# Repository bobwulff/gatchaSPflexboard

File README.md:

# gachaSP Flexboard

This is designed to be used with the Game Boy Advance SP mod created by [Joseph Tompkins](https://ko-fi.com/josephtomkins) called the [Gacha SP](https://www.youtube.com/watch?v=QM45YnBbGOQ).

This flexible circuit board should make wiring the button board to the main board a lot easier.

In addition to this flexboard you will need to source the following boards/parts:
|Part|Link|
|----|----|
|Faceplate and middle layer|[PCB Way](https://www.pcbway.com/project/shareproject/GachaSP_Final_Revision_a49df9d8.html)|
|PCB Board for rewiring (and wiring diagram)|[PCB Way](https://www.pcbway.com/project/shareproject/Custom_button_board_for_GachaSP_fa33171a.html)|
|Laminated GBA SP IPS Screen|[Retro Modding](https://www.retromodding.com/products/game-boy-advance-sp-ips-3-0inch-laminated-lcd)|
|Button Switches 4.8x4.8x4.5|[Aliexpress](https://www.aliexpress.us/item/3256804096997401.html?spm=a2g0o.order_list.order_list_main.29.59ec1802bsgRpf&gatewayAdapt=glo2usa)|
|Speaker|[eBay](https://www.ebay.com/itm/192292888553?_trkparms=amclksrc%3DITM%26aid%3D777008%26algo%3DPERSONAL.TOPIC%26ao%3D1%26asc%3D20230811123856%26meid%3Dfd54ea30a79047f3a256c025f49bf448%26pid%3D101770%26rk%3D1%26rkt%3D1%26itm%3D192292888553%26pmt%3D1%26noa%3D1%26pg%3D4375194%26algv%3DRecentlyViewedItemsV2&_trksid=p4375194.c101770.m146925&_trkparms=parentrq%3Aafa5a31518e0aab88905efafffffd88a%7Cpageci%3A49d20203-f37f-11ee-bd37-e2ac214ea922%7Ciid%3A1%7Cvlpname%3Avlp_homepage)|
|GBA SP Buttons|[Amazon, Affiliate](https://amzn.to/3TEVo3e)|

</br>
Newest version WITHOUT speaker contacts: </br>

</br></br>
Older version WITH speaker contacts: </br>

</br>

</br>

# To purchase
Download a zip file from the RELEASES section and upload straight to [PCB Way](https://pcbway.com) or [JLCPCB](https://jlcpcb.com). Make sure you select FLEX.
</br>

# Video Tutorial by Macho Nacho

</br>
GOOD LUCK!

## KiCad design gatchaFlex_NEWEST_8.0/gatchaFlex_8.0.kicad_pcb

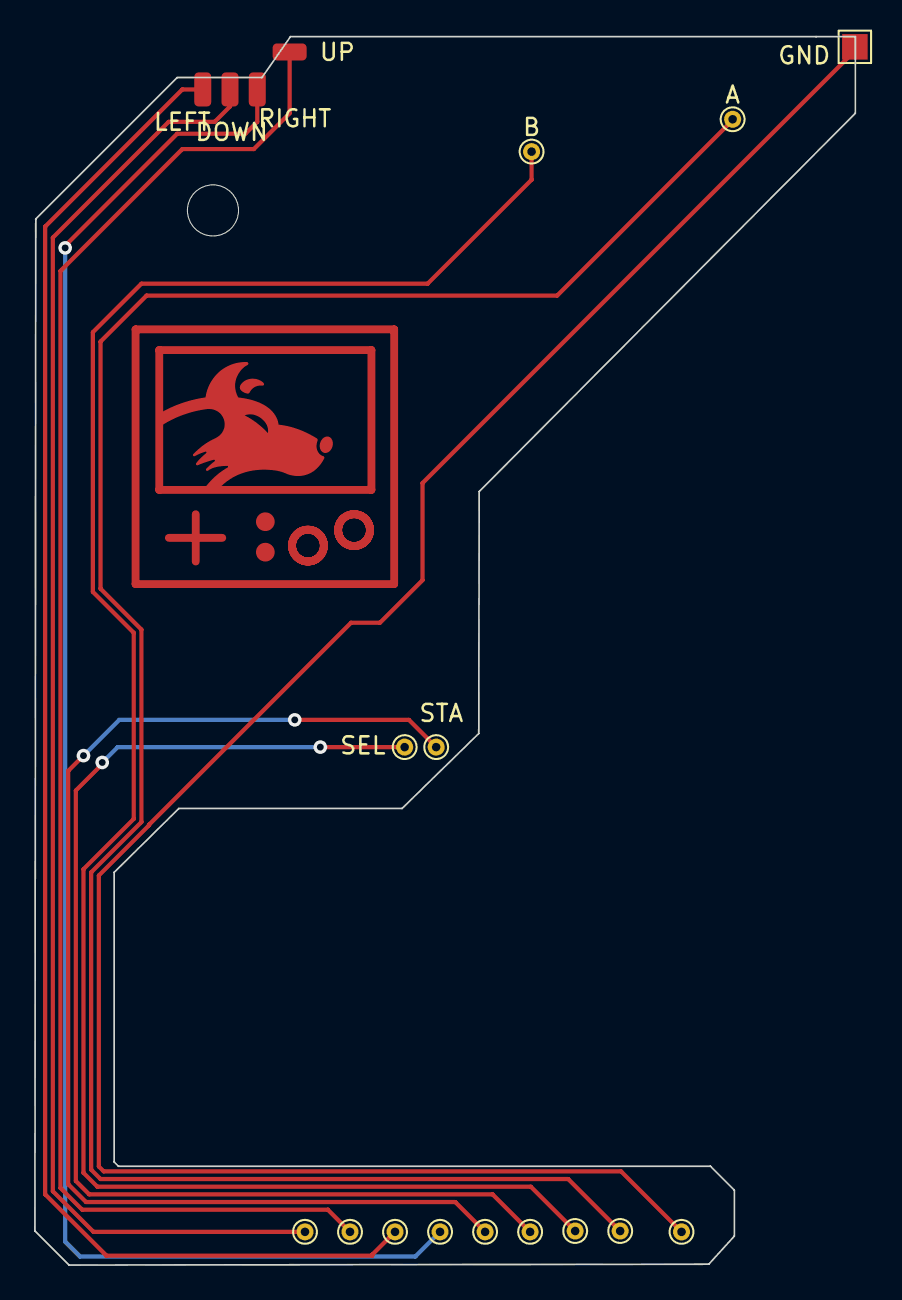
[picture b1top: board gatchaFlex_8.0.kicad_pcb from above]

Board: 2 copper layers, 48.2 x 72.1 mm, 19 parts (0 on the bottom side), 9 nets.

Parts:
A: TestPoint; TestPoint_THTPad_D1.0mm_Drill0.5mm
B: TestPoint; TestPoint_THTPad_D1.0mm_Drill0.5mm
DOWN: TestPoint; SolderWirePad_1x01_SMD_1x2mm
GND: TestPoint; TestPoint_Pad_1.5x1.5mm
GND2: TestPoint; TestPoint_THTPad_D1.0mm_Drill0.5mm
LEFT: TestPoint; SolderWirePad_1x01_SMD_1x2mm
LEFT#2: MountingHole_3mm
RIGHT: TestPoint; SolderWirePad_1x01_SMD_1x2mm
SEL: TestPoint; TestPoint_THTPad_D1.0mm_Drill0.5mm
STA: TestPoint; TestPoint_THTPad_D1.0mm_Drill0.5mm
TP8, TP9, TP10, TP11, TP12, TP13, TP14, TP15: TestPoint; TestPoint_THTPad_D1.0mm_Drill0.5mm
UP: TestPoint; SolderWirePad_1x01_SMD_1x2mm

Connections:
unnamed: GND.1, GND2.1
unnamed: A.1, TP8.1
unnamed: B.1, TP9.1
unnamed: SEL.1, TP10.1
unnamed: STA.1, TP11.1
unnamed: RIGHT.1, TP12.1
unnamed: LEFT.1, TP13.1
unnamed: DOWN.1, TP14.1
unnamed: TP15.1, UP.1

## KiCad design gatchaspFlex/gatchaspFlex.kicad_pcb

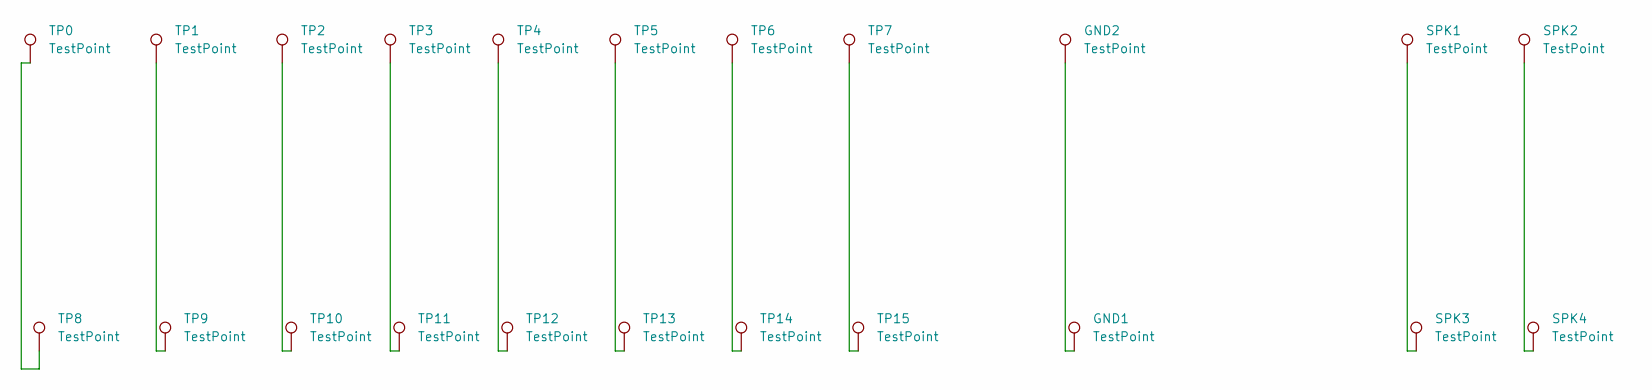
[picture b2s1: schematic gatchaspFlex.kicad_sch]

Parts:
GND1: TestPoint; TestPoint_Pad_1.5x1.5mm
GND2: TestPoint; TestPoint_THTPad_D1.0mm_Drill0.5mm
SPK1, SPK2, SPK3, SPK4: TestPoint; TestPoint_THTPad_D1.0mm_Drill0.5mm
TP0, TP1, TP2, TP3, TP8, TP9, TP10, TP11, TP12, TP13, TP14, TP15: TestPoint; TestPoint_THTPad_D1.0mm_Drill0.5mm
TP4, TP5, TP6, TP7: TestPoint; TestPoint-0.75mm

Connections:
unnamed: GND1.1, GND2.1
unnamed: SPK1.1, SPK3.1
unnamed: SPK2.1, SPK4.1
unnamed: TP0.1, TP8.1
unnamed: TP1.1, TP9.1
unnamed: TP2.1, TP10.1
unnamed: TP3.1, TP11.1
unnamed: TP4.1, TP12.1
unnamed: TP5.1, TP13.1
unnamed: TP6.1, TP14.1
unnamed: TP7.1, TP15.1

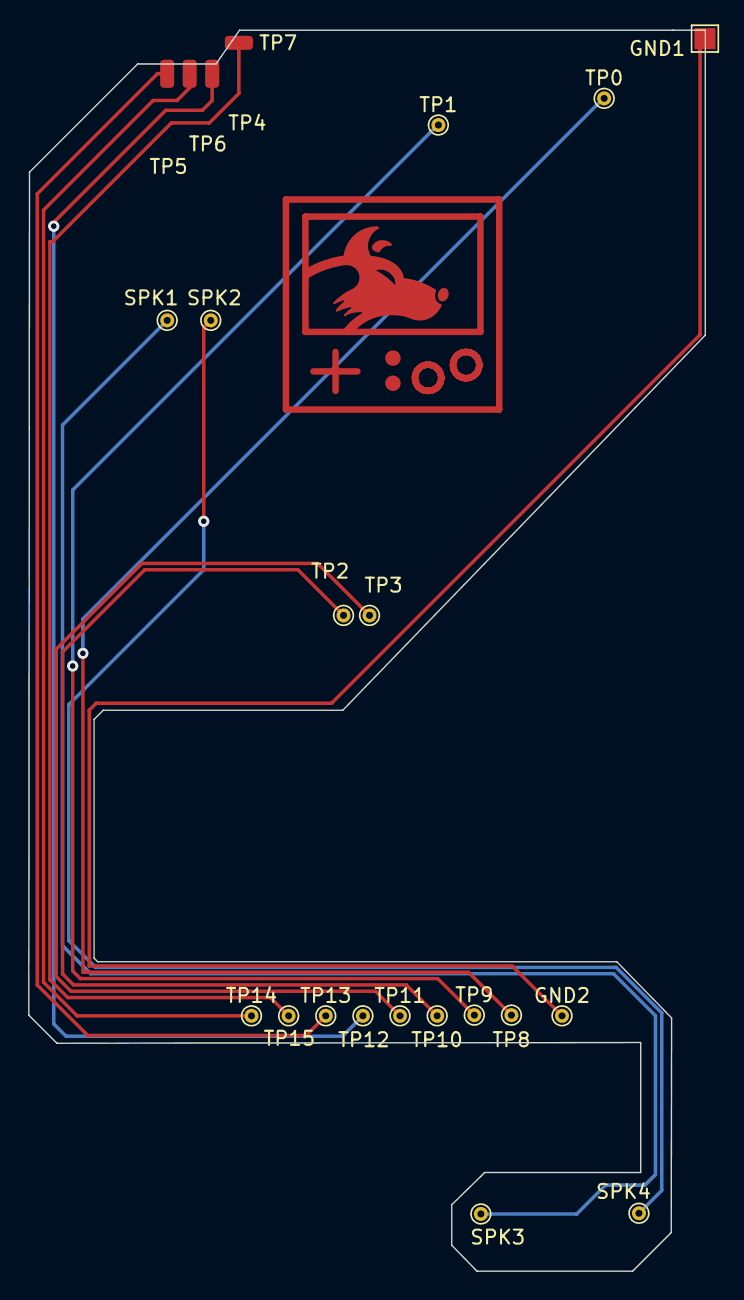
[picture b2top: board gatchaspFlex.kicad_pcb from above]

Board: 2 copper layers, 48.2 x 88.3 mm, 22 parts (0 on the bottom side), 11 nets.

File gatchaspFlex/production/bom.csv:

Designator,Footprint,Quantity,Value,LCSC Part #
GND1,TestPoint_Pad_1.5x1.5mm,1,TestPoint,
"GND2, SPK1, SPK2, SPK3, SPK4, TP0, TP1, TP10, TP11, TP12, TP13, TP14, TP15, TP2, TP3, TP8, TP9",TestPoint_THTPad_D1.0mm_Drill0.5mm,17,TestPoint,

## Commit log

2024-04-04 Updated readme with more info, added list of items needed for the project, added a link to Joseph Tompkins' KoFi, link to WulffDen video to show the mod itself, added a table for the parts list, upda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
2024-04-04 The table was ugly
2024-04-04 Added a link to the rubber membranes
2024-04-05 Update README.md
    updated pcb way links
2024-04-08 Fix documentation
